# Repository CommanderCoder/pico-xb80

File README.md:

# pico-xb80

pico-xb80 is a small expansion-bus interface for 1970s and 1980s desktop machines, designed to allow a Raspberry Pi Pico 2 board to present an SD card-backed storage device to a Sharp MZ80K system.

https://youtu.be/xSwXQkPeJl4?si=bnu4Bi942s_XvJiR

## Supported hardware

Currently supported:

* [Sharp MZ80K](https://en.wikipedia.org/wiki/Sharp_MZ)

Possible future targets with additional effort:

* [Tandy TRS-80 and clones](https://en.wikipedia.org/wiki/List_of_TRS-80_clones)

## What it does

The project uses a Pico 2 board and an SD card to provide a file system to the Sharp MZ80K through the expansion bus. A small monitor ROM extension and host-side software allow the machine to access files stored on an SD card in a way that is compatible with the existing monitor and tape-handling model.

The software stack includes:

* SD card interface support for the Pico 2 board configuration used here, over hardware SPI where the wiring allows it and bit-banged 1-bit native SD mode otherwise
* `fatfs` by ChaN
* a custom expansion-bus implementation using the Pico PIO and DMA subsystems
* Sharp MZ80K-specific glue logic and ROM support for monitor commands such as `*FD`

## Hardware overview

Off-the-shelf components are used to keep the project accessible and inexpensive.

* Raspberry Pi Pico 2 / RP2350B mounted on an [Olimex Pico2-XXL](https://www.olimex.com/Products/RaspberryPi/PICO/PICO2-XXL/open-source-hardware)
* SD card socket mounted on the board
* Ribbon cable and jumper wires to connect the bus to the computer
  * Sharp MZ80K uses a [50-way ribbon cable](https://www.google.com/search?q=50+way+ribbon+cable)
  * [DuPont or similar jump wires](https://en.wikipedia.org/wiki/Jump_wire)

This is a prototype-style design intended to be simple to build and experiment with. A dedicated single-board version may be possible in the future, but the current approach uses the Olimex board for flexibility.

## Development environment

The project is built and developed with:

* VS Code
* Raspberry Pi Pico SDK
* Git - [git in VSCode](https://code.visualstudio.com/docs/sourcecontrol/overview) 
* Python 3

### Z80 code tooling

> Important: you will need to build your own copy of `sjasmplus` for your platform.

The repository includes support for:

* [sjasmplus](https://github.com/z00m128/sjasmplus) for assembling Z80 code into machine-code binaries
* `bin2header.py` to convert binary output into a C header suitable for inclusion in the Pico firmware

## Utility tools

The project includes a small set of helper scripts for working with Sharp MZ80K file images:

* `filehandle_path.py` — scans a Sharp MZ80K binary for tape-handler calls and rewrites them to use the SD-backed handlers
* `mz_tape_info.py` — inspects file images and reports the file type plus whether they have already been patched

# Build and upload

## Wiring

Only the right-hand column of pins is used from EXT1 and EXT2 on the Olimex board.

<div style="display: flex; gap: 1rem;">
  <div style="flex: 1;">

| Olimex EXT1 | MZ80K | XB Signal |
|----------|----------|----------|
| P1 | nc | |
| P3 | A25 (mark) | D0 |
| P5 | A24 | D1 |
| P7 | A23 | D2 |
| P9 | A22 | D3 |
| P11 | A21 | D4 |
| P13 | A20  | D5 |
| P15 | A19 | D6 |
| P17 | A18 | D7 |
| P19 | nc | |
| P21 | nc | |
| P23 | nc | |
| P25 | nc | |
| P27 | nc | |
| P29 | nc | |
| P31 | B10 | NWR |
| P33 | B8 | NRD |
| P35 | B6 | NIOREQ |
| P37 | B4 | NMREQ |
| P39 | B3 | GND |

  </div>

  <div style="flex: 1;">

| Olimex EXT2 | MZ80K | Signal |
|----------|----------|----------|
| P1 | nc | |
| P3 | A16 | A0 |
| P5 | A15 | A1 |
| P7 | A14 | A2 |
| P9 | A13 | A3 |
| P11 | A12 | A4 |
| P13 | A11 | A5 |
| P15 | A10 | A6 |
| P17 | A9 | A7 |
| P19 | nc | |
| P21 | nc | |
| P23 | A8 | A8 |
| P25 | A7 | A9 |
| P27 | A6 | A10 |
| P29 | A5 | A11 |
| P31 | A4 | A12 |
| P33 | A3 | A13 |
| P35 | A2 | A14 |
| P37 | A1 | A15 |
| P39 | nc | |

  </div>
</div>

## Building

From the project root:

```bash
cmake -S . -B build -G Ninja
cmake --build build
```

## Uploading

To put the Pico into bootloader mode:

* hold the BOOT button
* connect the board to your computer via USB

Then upload the firmware using VS Code with the Pico extension, or use the project task configuration already provided in the workspace.

## SD card layout

Create an SD card with a root-level folder named `MZ_FD`. Place the files you want to access inside that directory and give them the `.MZF` extension. The file `0000.MZF` is loaded whenever `*FD` is used from the monitor.

## Patch workflow

Because the monitor ROM cannot be modified in software, a replacement ROM or a patched program image is required to redirect tape-file operations to the SD-backed handlers.

The helper scripts make this easier:

* `mz_tape_info.py` identifies files that use tape-file logic
* `filehandle_path.py` patches those files to call the SD-handler routines instead

## Power

The board can be powered either from the host laptop USB port or from a standard USB power supply.

# Operating instructions

See [OPERATING.md](OPERATING.md) for instructions on using the interface from the Sharp monitor ROM.

# Reference and acknowledgements

Thanks to:

* [MZ80K_SD](https://github.com/yanataka60/MZ80K_SD)
* [Atom-DVI](https://github.com/cmoulang/Atom-DVI)
* [MZ-80A](https://mz-80a.com/)
* [MZ-Archive](https://mz-archive.co.uk/)
* [Sharp MZ](https://www.sharpmz.net/)
* the wider retro-computing community for technical discussion and reference material

This project also benefited from discussions and examples from several AI systems used during development, but the project itself is intended to stand on its own technical merits.

# Technical notes

## The software:
* SD Card interface software (initially from prompts to Claude.ai).  The Olimex Pico2-XXL has two variants.  One use 1-bit communication protocol and the other uses the 4-bit protocol.  My board used 1-bit so the software was originally built for this.

  `SdCard::detect_board_revision()` works out which board it is running on first, since the two Olimex revisions wire the card differently.  Revision A puts SD_DAT0 on GPIO12 and leaves R24 - the link between GPIO9 and the card's CS pin - unpopulated, so it can only be bit-banged.  Revision B moved SD_DAT0 to GPIO24 (GPIO12 collides with the RP2350's HSTX/HDMI block) and ships wired for SPI.  The check is electrical, not a conversation with the card: it looks for the 10k pull-up the SD_DAT0 net carries on the board, so it needs no card in the socket and sends no commands - which matters, because a `CMD0` seen with CS low latches a card into SPI mode until it is next powered down.

  That gives two transports, picked at startup by `SdCard::initialize()`:
  * **SPI** - used on Revision B.  The card is driven by one of the RP2350 SPI blocks, so a sector moves as 512 hardware-clocked bytes at 12.5MHz rather than 4096 bit-banged GPIO transitions.  This needs CS on a GPIO and CLK/DI/DO on pins that can carry the SCK/TX/RX functions of a single SPI instance - GPIO9/10/11/24 are all `spi1`, so they qualify.
  * **1-bit native SD** - used on Revision A, and the fallback everywhere else: whenever the wiring cannot carry SPI or the card does not answer the SPI probe.  CMD/CLK/DAT0 are bit-banged at roughly 500kHz with the CPU busy-waiting for the whole sector.

  If the detected wiring fails to initialise, the other revision's wiring is tried before giving up.

* Expansion Bus - provides a shared memory on the address bus.  [Pico PIOs](https://www.raspberrypi.com/news/what-is-pio/) rapidly reads addresses and data which several DMAs pump in and out of 64Kx16bit words (128Kb).
  * heavily influenced by [ATOM-DVI](https://github.com/cmoulang/Atom-DVI) after speaking with Chris about his project at an ABUG event. 
* pico-xb80_mz80k - the specific Sharp MZ80K interface.  
  * Z80 *ROM* this is shared on the bus at `0xF000` so that the Monitor ROM can jump to it with an `*FD` command.
  * Mailbox addresses so that the Z80 can send and receive commands and data to/from the Pico
  * Communcation with the SD card via the SD Card interface and `fatfs`

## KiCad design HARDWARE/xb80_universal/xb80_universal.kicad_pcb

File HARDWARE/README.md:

# Hardware

## Revision 1 schematic

The [`xb80_universal.pdf`](xb80_universal.pdf) file contains the first hardware revision schamatic design for the board.

## Revision 1 visual reference

Render of the assembled first-revision board layout and component placement for quick visual reference.

Pico on top with headers underneath.  Ribbon cable underneath that.

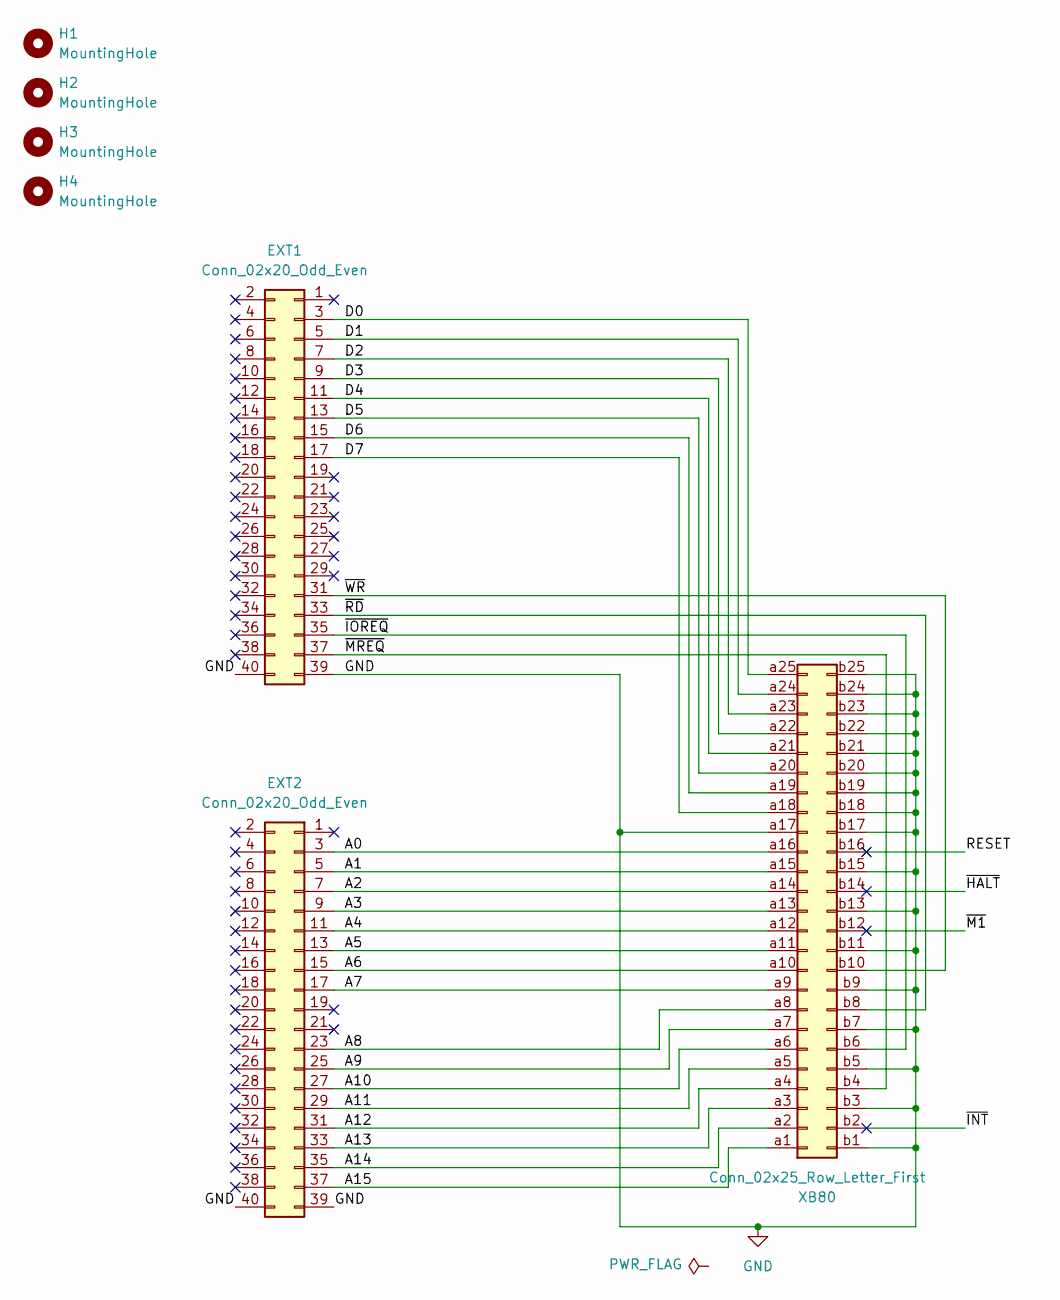
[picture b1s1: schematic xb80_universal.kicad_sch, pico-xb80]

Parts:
EXT1, EXT2: Conn_02x20_Odd_Even; PinSocket_2x20_P2.54mm_Vertical
H1, H2, H3, H4: MountingHole; MountingHole_2.7mm_M2.5
XB80: Conn_02x25_Row_Letter_First; IDC-Header_2x25_P2.54mm_Vertical

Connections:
/A0: EXT2.3, XB80.a16
/A1: EXT2.5, XB80.a15
/A2: EXT2.7, XB80.a14
/A3: EXT2.9, XB80.a13
/A4: EXT2.11, XB80.a12
/A5: EXT2.13, XB80.a11
/A6: EXT2.15, XB80.a10
/A7: EXT2.17, XB80.a9
/A8: EXT2.23, XB80.a8
/A9: EXT2.25, XB80.a7
/A10: EXT2.27, XB80.a6
/A11: EXT2.29, XB80.a5
/A12: EXT2.31, XB80.a4
/A13: EXT2.33, XB80.a3
/A14: EXT2.35, XB80.a2
/A15: EXT2.37, XB80.a1
/D0: EXT1.3, XB80.a25
/D1: EXT1.5, XB80.a24
/D2: EXT1.7, XB80.a23
/D3: EXT1.9, XB80.a22
/D4: EXT1.11, XB80.a21
/D5: EXT1.13, XB80.a20
/D6: EXT1.15, XB80.a19
/D7: EXT1.17, XB80.a18
/RESET: XB80.b16
/~HALT: XB80.b14
/~INT: XB80.b2
/~IOREQ: EXT1.35, XB80.b6
/~M1: XB80.b12
/~MREQ: EXT1.37, XB80.b4
/~RD: EXT1.33, XB80.b8
/~WR: EXT1.31, XB80.b10
GND: EXT1.39, EXT1.40, EXT2.39, EXT2.40, XB80.a17, XB80.b1, XB80.b3, XB80.b5, XB80.b7, XB80.b9, XB80.b11, XB80.b13, XB80.b15, XB80.b17, XB80.b18, XB80.b19, XB80.b20, XB80.b21, XB80.b22, XB80.b23, XB80.b24, XB80.b25

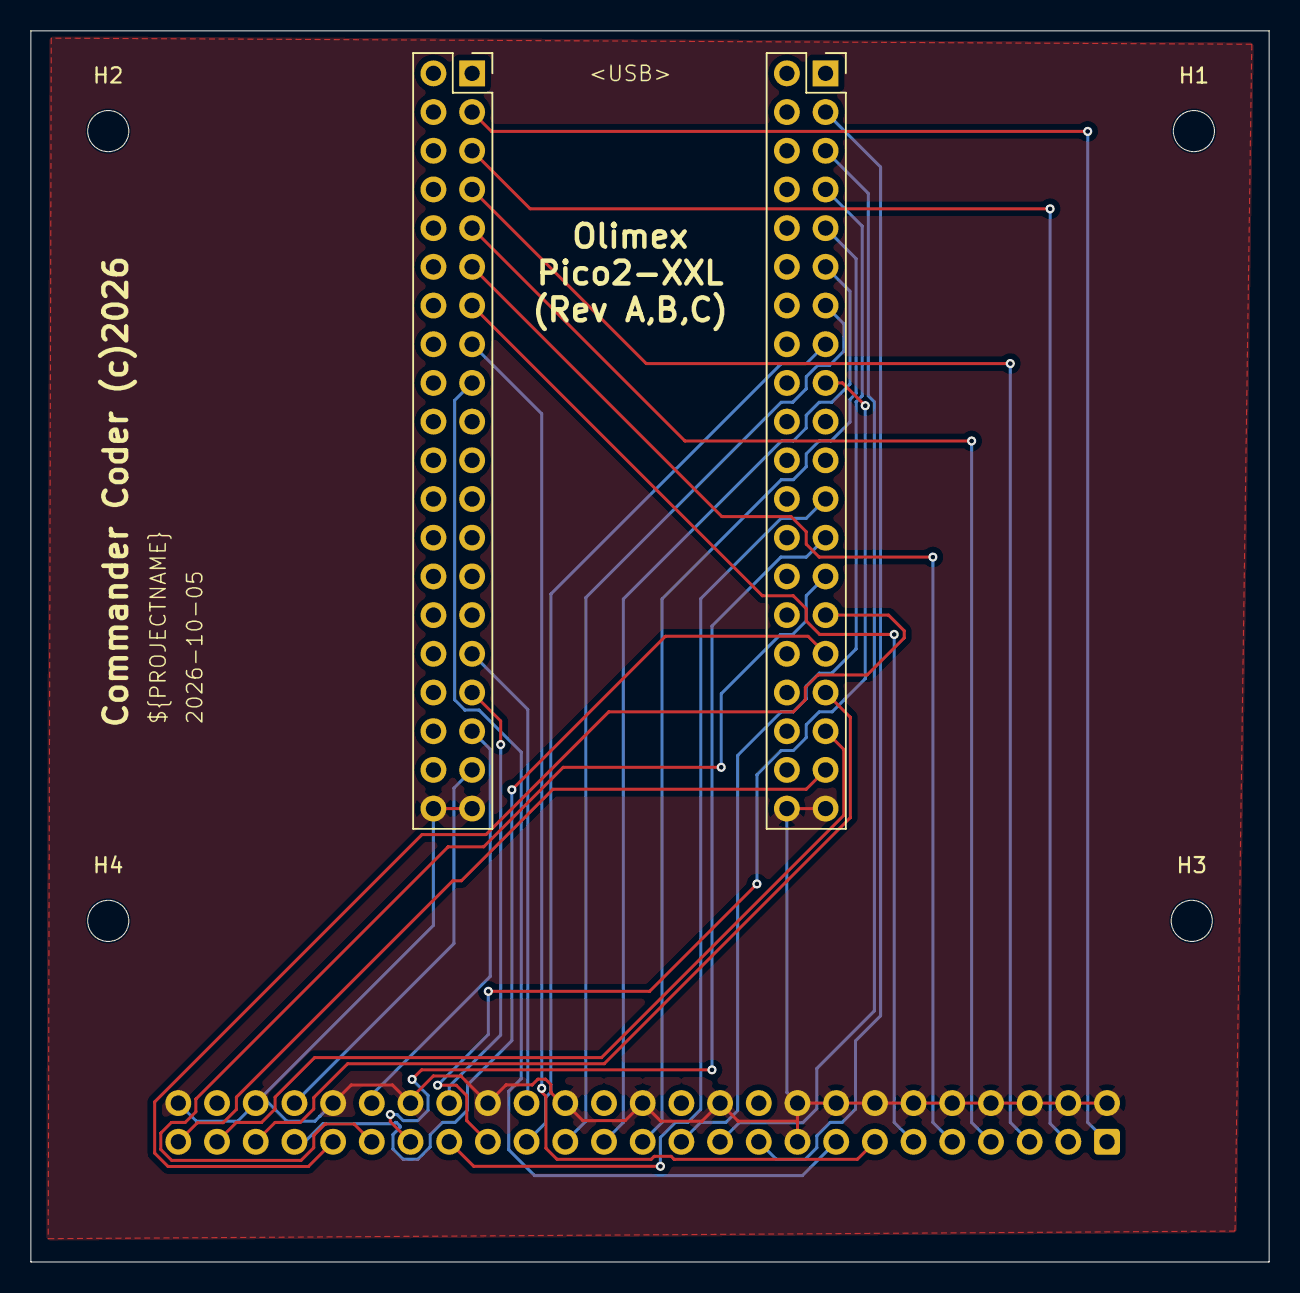
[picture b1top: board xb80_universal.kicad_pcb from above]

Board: 2 copper layers, 81.3 x 80.8 mm, 7 parts (1 on the bottom side), 29 nets.

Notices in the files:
HARDWARE/xb80_universal/xb80_universal.kicad_pcb:
Commander Coder (c)2026
